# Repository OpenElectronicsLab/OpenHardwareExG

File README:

The OpenHardwareExG is a platform for ECG, EEG, EMG, ENG, EOG, and evoked potential applications.

http://openelectronicslab.github.io/OpenHardwareExG/

The OpenHardwareExG platform was originally developed as part of the eeg-mouse project.
https://github.com/OpenElectronicsLab/eeg-mouse

Software License

GPL v3 or any later version

(The authors may be persuaded to license parts of their contributions
under another FOSS license if GPLv3 is a problem for integration with an
existing established project, for instance linux kernel is GPLv2. Please
contact us.) Hardware and Hardware Documentation License

CERN Open Hardware Licence

(This applies mostly to the kicad-files and scad-files directories)
"Documentation" means schematic diagrams, designs, circuit or circuit
board layouts, mechanical drawings, flow charts and descriptive text,
and other explanatory material that is explicitly stated as being made
available under the conditions of this Licence. The Documentation may be
in any medium, including but not limited to computer files and
representations on paper, film, or any other media.

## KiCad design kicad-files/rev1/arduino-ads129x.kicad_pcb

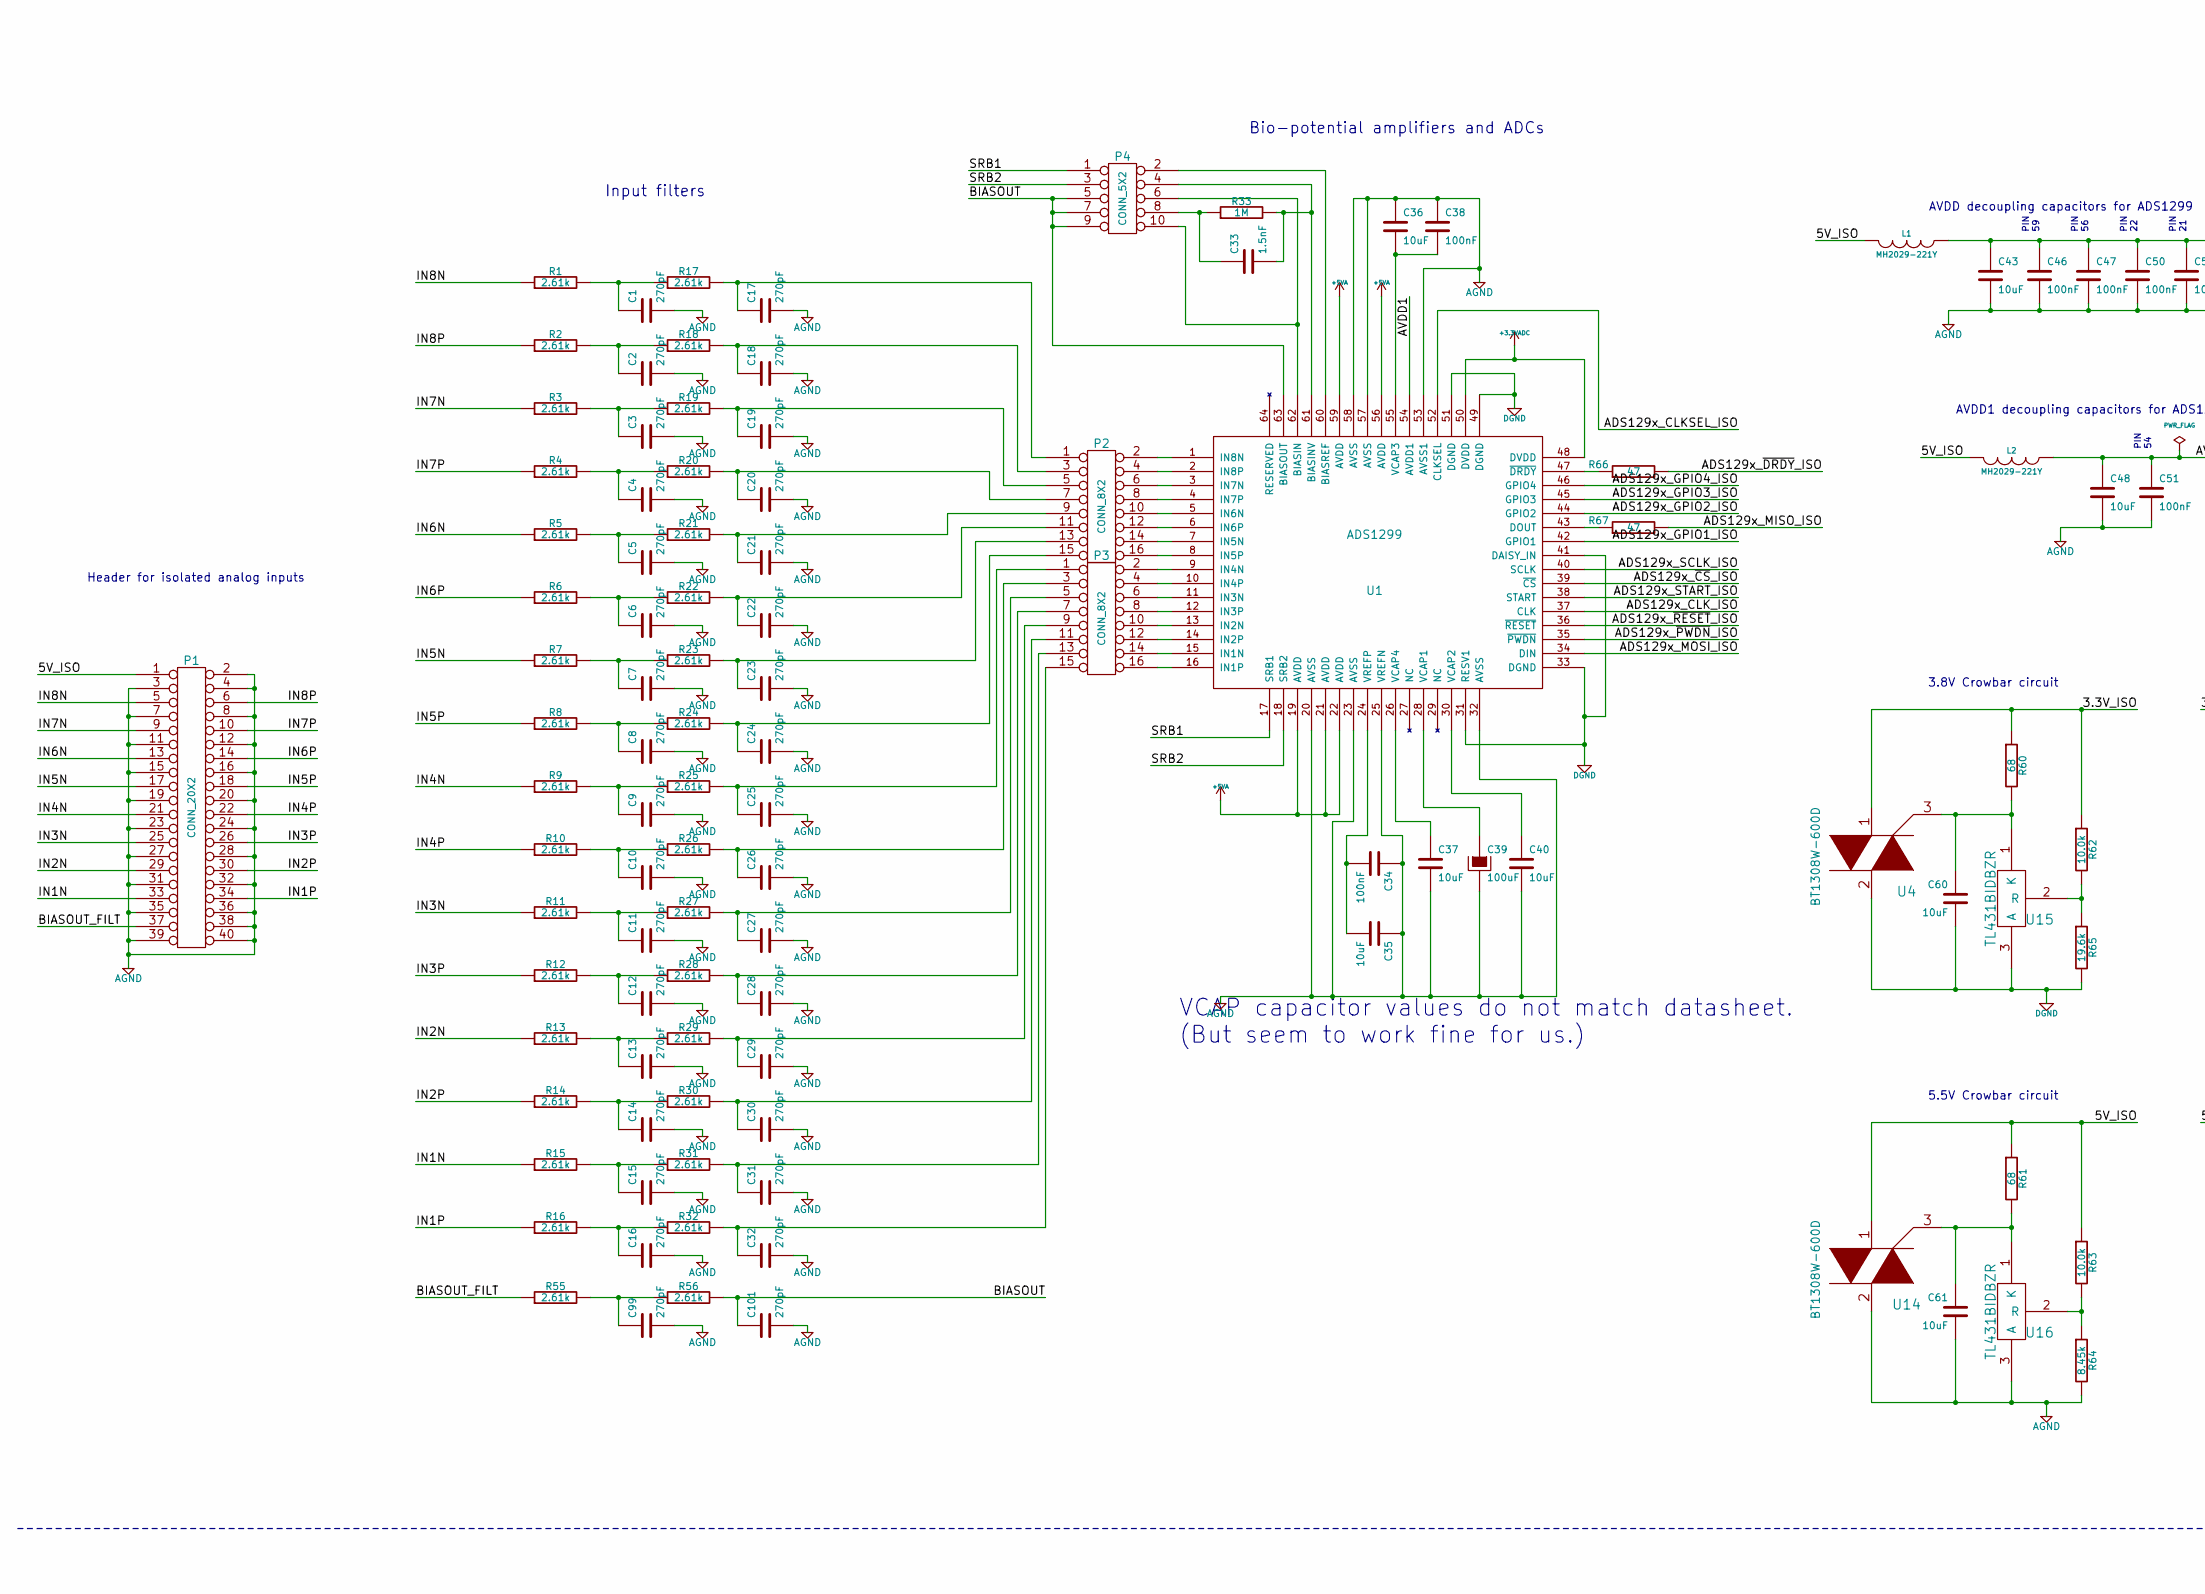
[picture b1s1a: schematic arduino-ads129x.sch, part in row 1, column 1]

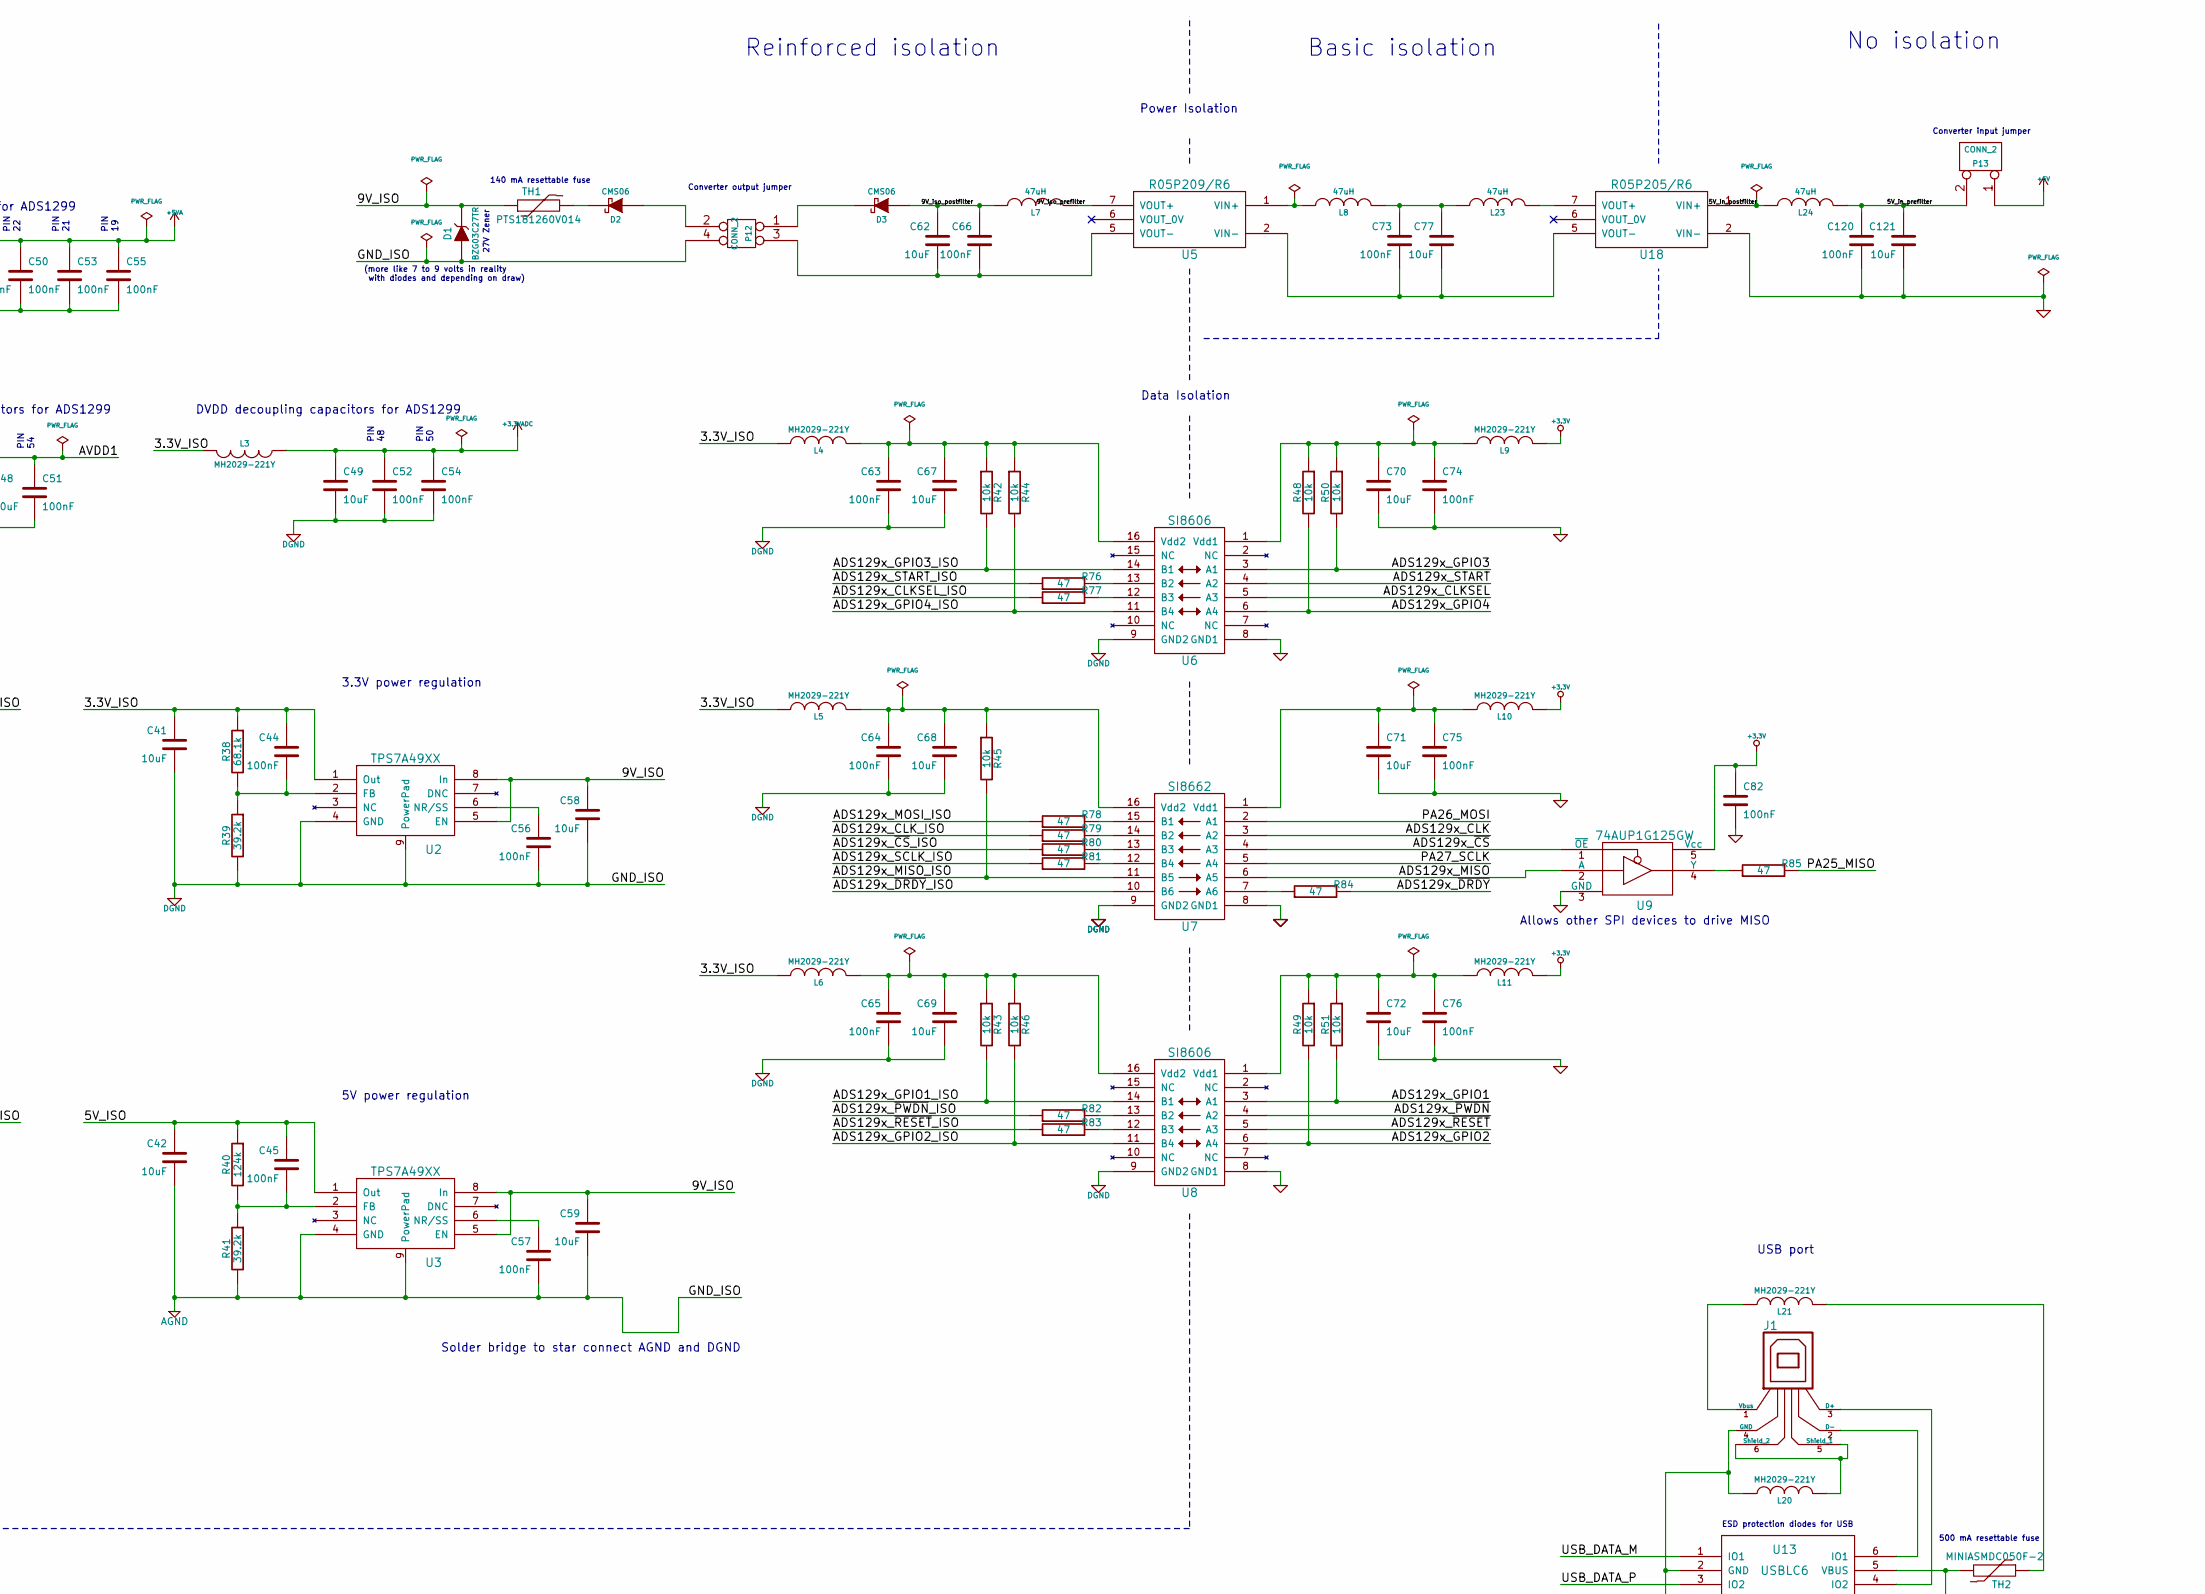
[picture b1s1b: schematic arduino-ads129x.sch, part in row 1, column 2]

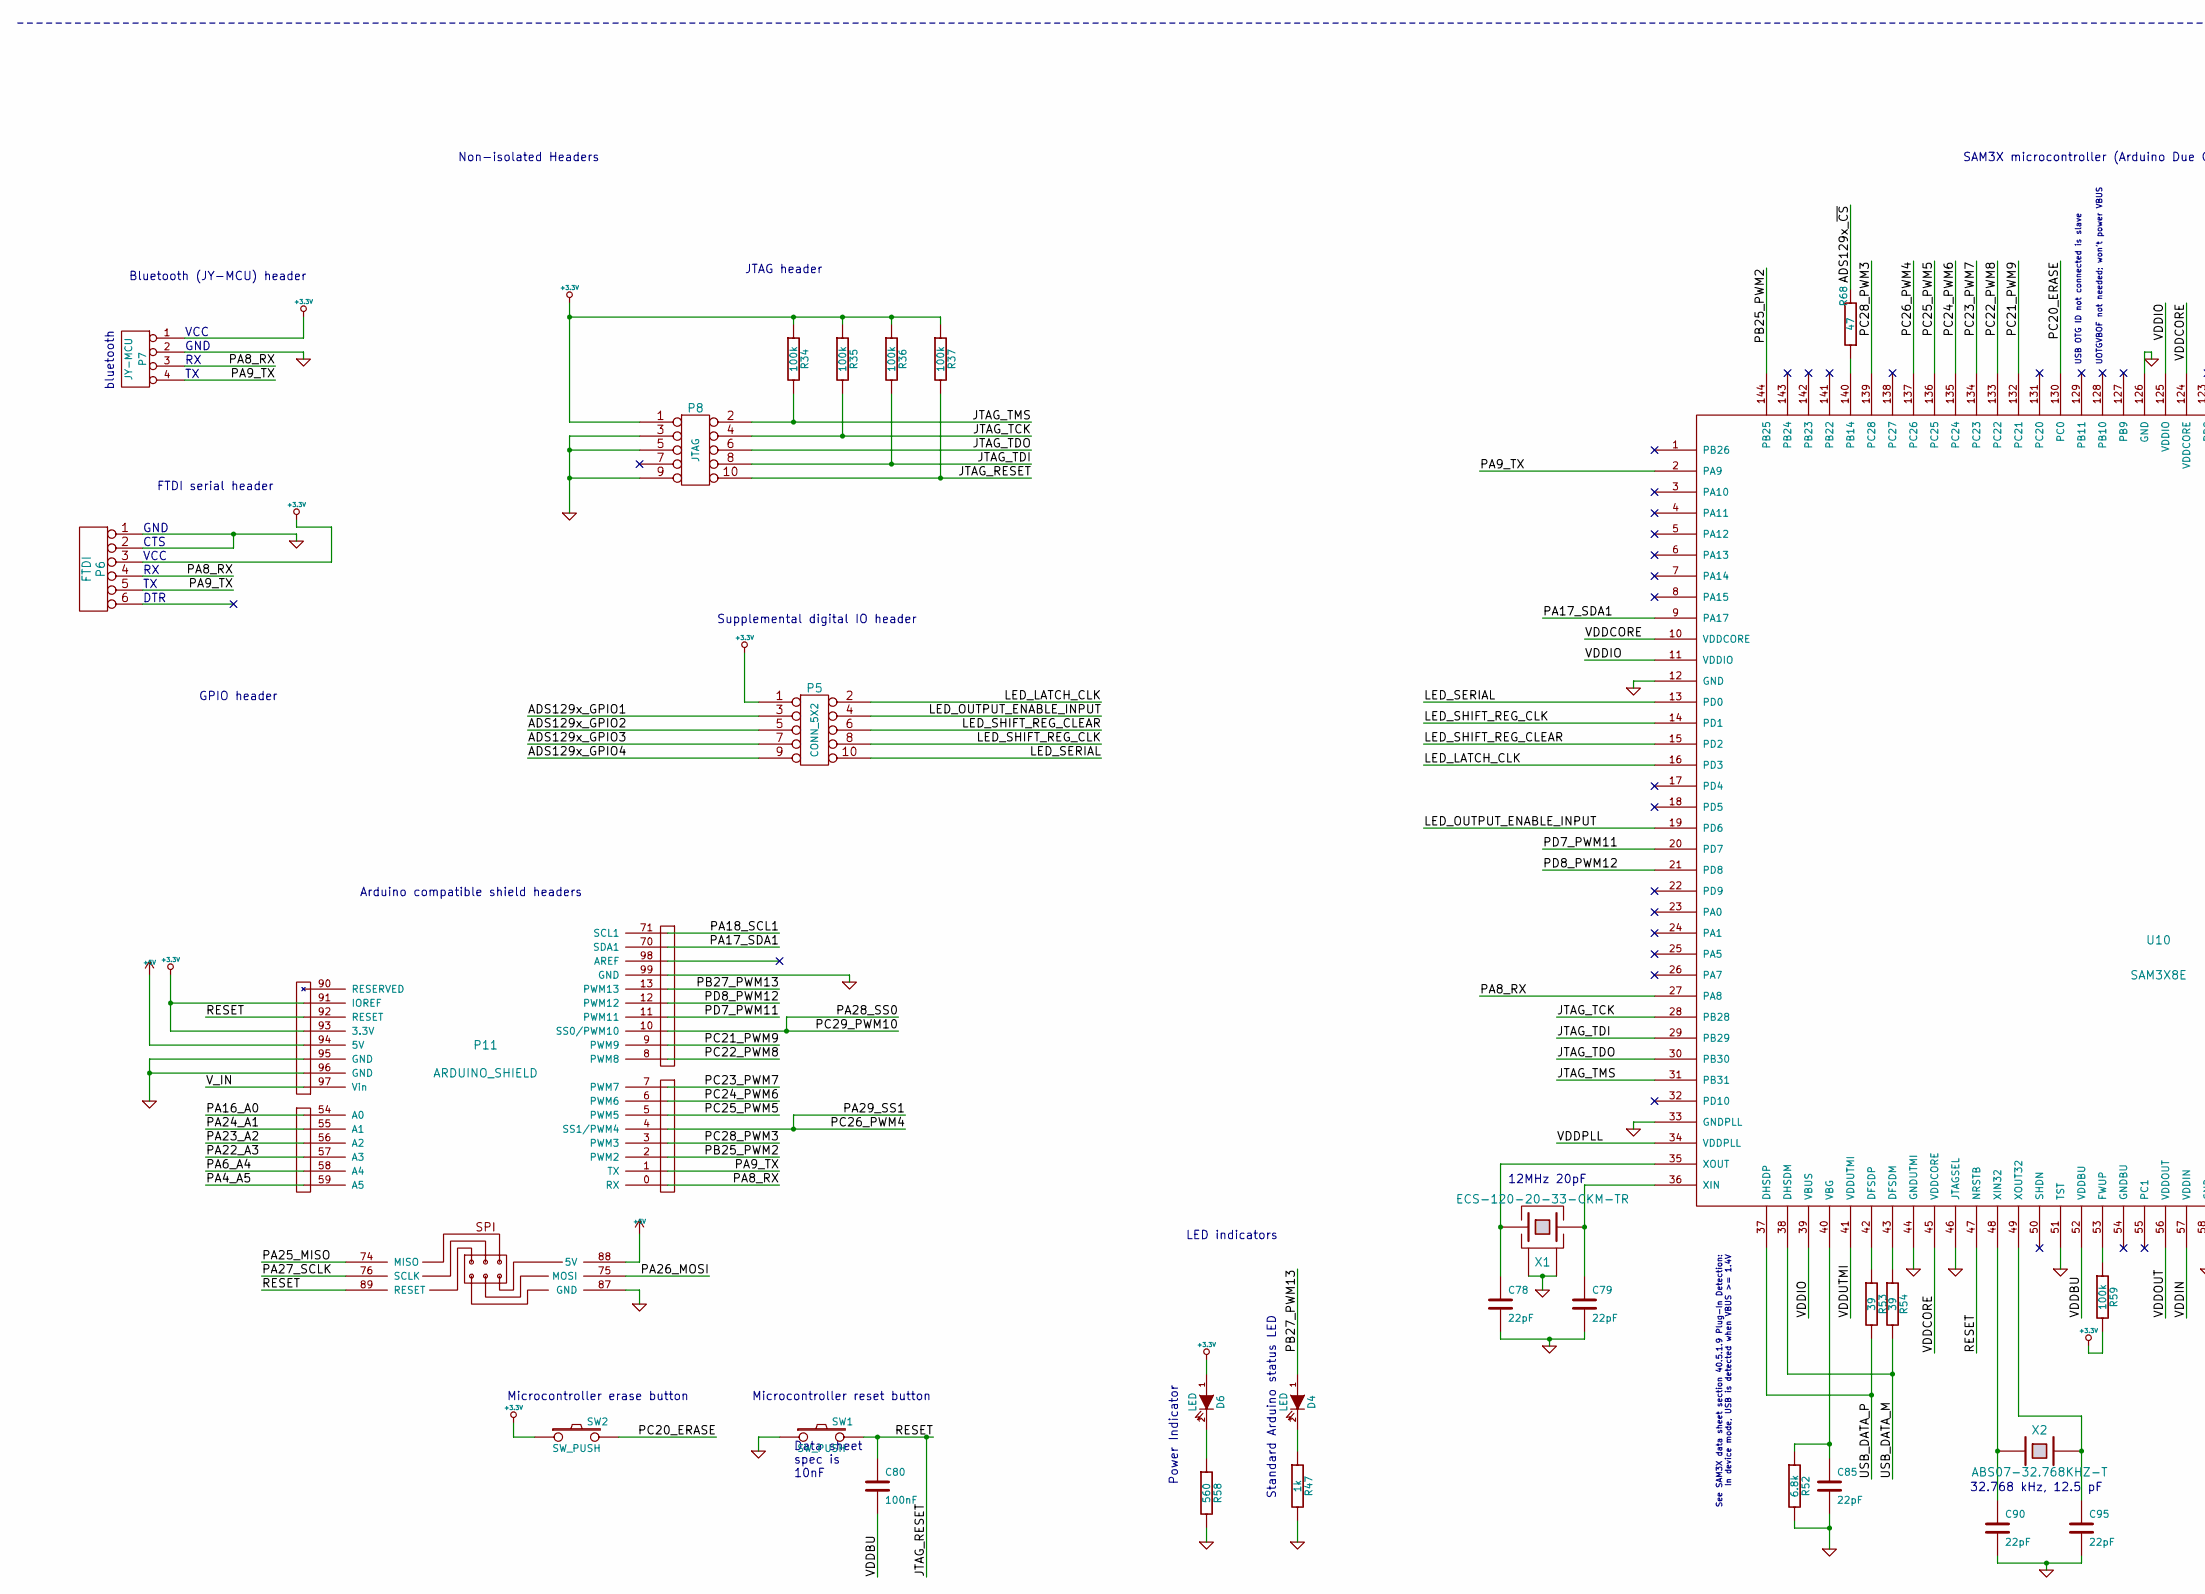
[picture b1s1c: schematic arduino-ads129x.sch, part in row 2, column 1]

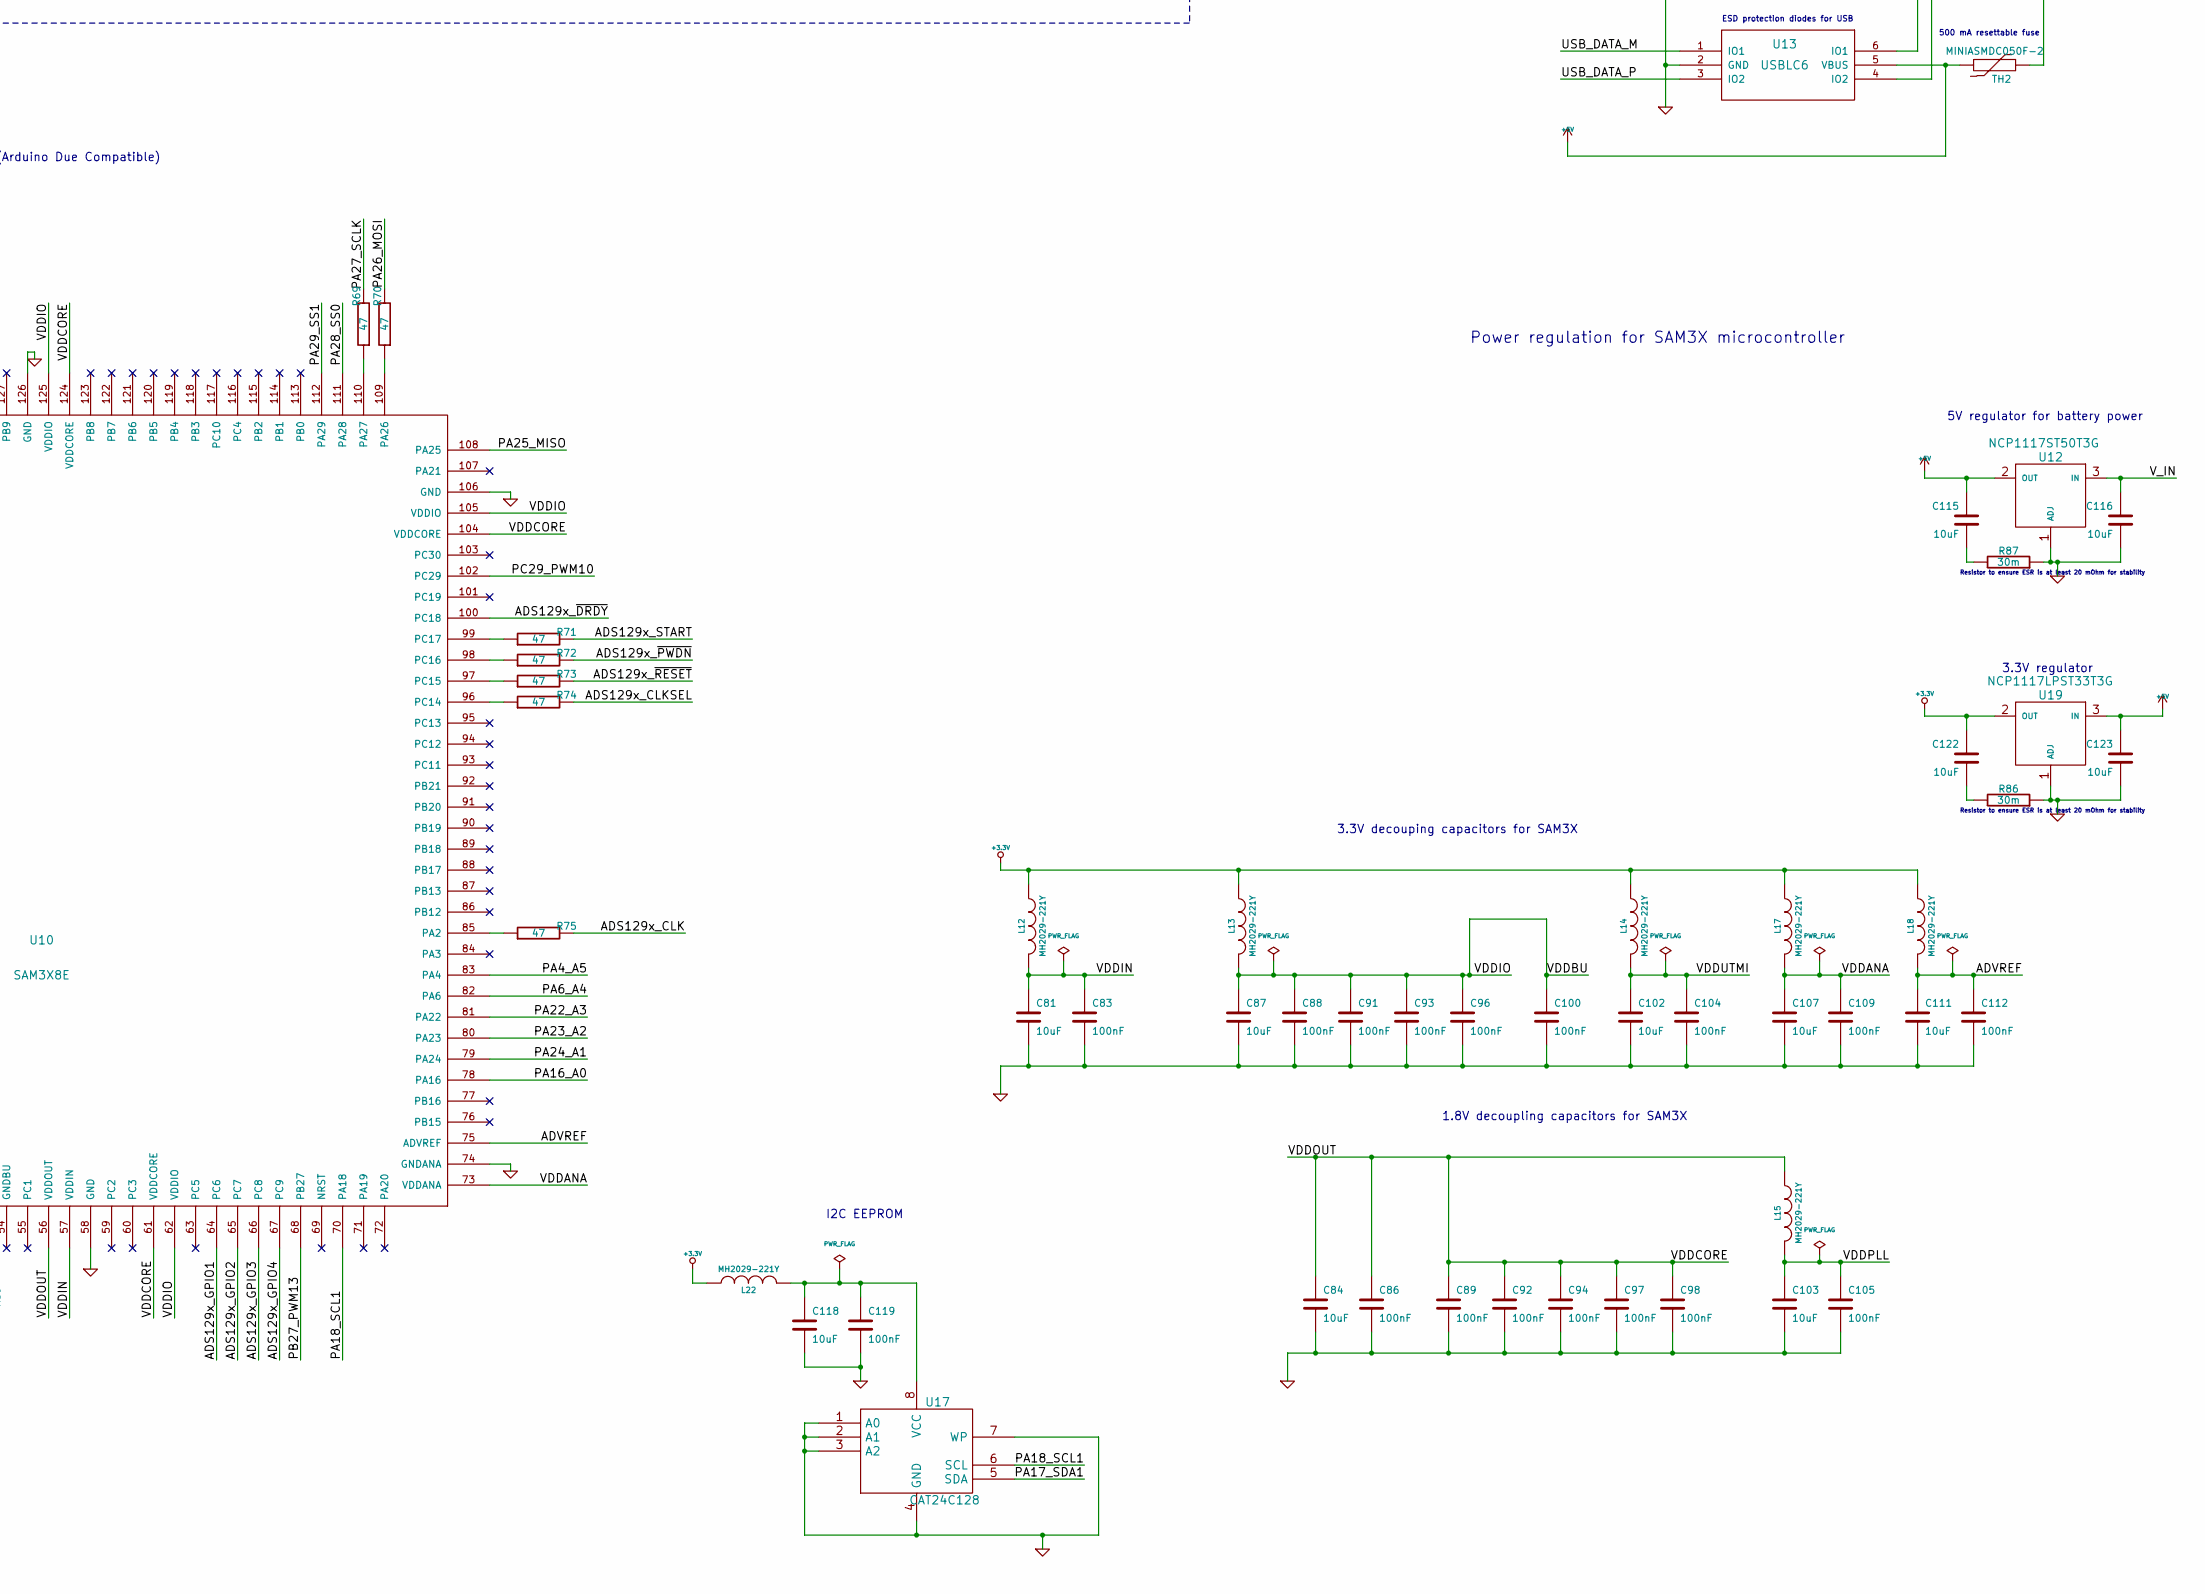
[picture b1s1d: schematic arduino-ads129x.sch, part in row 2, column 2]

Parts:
C1, C2, C3, C4, C5, C6, C7, C8, C9, C10, C11, C12, C13, C14, C15, C16, C17, C18, C19, C20, C21, C22, C23, C24, C25, C26, C27, C28, C29, C30, C31, C32, C99, C101: 270pF; SM0603
C33: 1.5nF; SM0603
C34, C38, C44, C45, C46, C47, C50, C51, C52, C53, C54, C55, C56, C57, C63, C64, C65, C66, C73, C74, C75, C76, C80, C82, C83, C86, C88, C89, C91, C92, C93, C94, C96, C97, C98, C100, C104, C105, C109, C112, C119, C120: 100nF; SM0603
C35, C36, C37, C40, C41, C42, C43, C48, C49, C60, C61, C67, C68, C69, C70, C71, C72, C77, C81, C84, C87, C102, C103, C107, C111, C115, C118, C121, C122, C123: 10uF; SM0805
C39: 100uF; SM2512
C58, C59, C62, C116: 10uF; SM1210
C78, C79, C85, C90, C95: 22pF; SM0603
D1: BZG03C27TR; DO214
D2, D3: CMS06; SM2010
D4, D6: LED; LED-0603
J1: USB; USB_B
L1, L2, L3, L4, L5, L6, L9, L10, L11, L12, L13, L14, L15, L17, L18, L20, L21, L22: MH2029-221Y; SM0805
L7, L8, L23, L24: 47uH; SRR4028
P1: CONN_20X2; PIN_ARRAY_20X2
P2, P3: CONN_8X2; pin_array_8x2
P4, P5: CONN_5X2; PIN_ARRAY_5x2
P6: FTDI; PIN_ARRAY-6X1
P7: JY-MCU; PIN_ARRAY_4x1
P8: JTAG; SMT_PIN_2x5
P11: ARDUINO_SHIELD; arduino_shield
P12: CONN_2; PIN_ARRAY_2X2
P13: CONN_2; PIN_ARRAY_2X1
R1, R2, R3, R4, R5, R6, R7, R8, R9, R10, R11, R12, R13, R14, R15, R16, R17, R18, R19, R20, R21, R22, R23, R24, R25, R26, R27, R28, R29, R30, R31, R32, R55, R56: 2.61k; SM0603
R33: 1M; SM0805
R34, R35, R36, R37, R59: 100k; SM0603
R38: 68.1k; SM0603
R39, R41: 39.2k; SM0603
R40: 124k; SM0603
R42, R43, R44, R45, R46, R48, R49, R50, R51: 10k; SM0603
R47: 1k; SM0603
R52: 6.8k; SM0603
R53, R54: 39; SM0603
R58: 560; SM0603
R60, R61: 68; SM0603
R62, R63: 10.0k; SM0603
R64: 8.45k; SM0603
R65: 19.6k; SM0603
R66, R67, R68, R69, R70, R71, R72, R73, R74, R75, R76, R77, R78, R79, R80, R81, R82, R83, R84, R85: 47; SM0603
R86, R87: 30m; SM0603
SW1, SW2: SW_PUSH; smt-tactile-button
TH1: PTS181260V014; SM1812
TH2: MINIASMDC050F-2; SM1812
U1: ADS1299; TQFP_64
U2, U3: TPS7A49XX; MSOP8_PowerPad
U4, U14: BT1308W-600D; SOT223
U5: R05P209/R6; SIP7_ISOLATOR
U6, U8: SI8606; SO16W
U7: SI8662; SO16W
U9: 74AUP1G125GW; SOT353
U10: SAM3X8E; TQFP144
U12: NCP1117ST50T3G; SOT223
U13: USBLC6; SOT23_6
U15, U16: TL431BIDBZR; SOT23
U17: CAT24C128; SOIC8
U18: R05P205/R6; SIP7_ISOLATOR
U19: NCP1117LPST33T3G; SOT223
X1: ECS-120-20-33-CKM-TR; smt-crystal-3.2x2.5
X2: ABS07-32.768KHZ-T; ABS07

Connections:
+3.3V: C82.1, C122.1, D6.1 (A), L9.2, L10.2, L11.2, L12.1, L13.1, L14.1, L17.1, L18.1, L22.1, P5.1, P6.3, P7.1, P8.1, P11.91 (IOREF), P11.93 (3.3V), R34.1, R35.1, R36.1, R37.1, R59.2, SW2.1, U9.5 (Vcc), U19.2 (OUT)
+3.3VADC: C49.1, C52.1, C54.1, L3.1, U1.48 (DVDD), U1.50 (DVDD)
+5V: C115.1, C123.1, P11.88 (5V), P11.94 (5V), P13.1, TH2.2, U12.2 (OUT), U13.5 (VBUS), U19.3 (IN)
+5VA: C43.1, C46.1, C47.1, C50.1, C53.1, C55.1, L1.1, U1.19 (AVDD), U1.21 (AVDD), U1.22 (AVDD), U1.56 (AVDD), U1.59 (AVDD)
/3.3V_ISO: C41.1, C44.1, L3.2, L4.2, L5.2, L6.2, R38.1, R60.1, R62.1, U2.1 (Out), U4.1
/5V_ISO: C42.1, C45.1, L1.2, L2.2, P1.1, R40.1, R61.1, R63.1, U3.1 (Out), U14.1
/5V_in_prefilter: C120.1, C121.1, L24.1, P13.2 (PM)
/9V_ISO: C58.1, C59.1, D1.2 (K), TH1.1, U2.5 (EN), U2.8 (In), U3.5 (EN), U3.8 (In)
/9V_iso_postfilter: C62.1, C66.1, D3.1 (A), L7.2
/ADS129x_CLK: R75.2, U7.3 (A2)
/ADS129x_CLKSEL: R74.2, U6.5 (A3)
/ADS129x_CLKSEL_ISO: R77.1, U1.52 (CLKSEL)
/ADS129x_CLK_ISO: R79.1, U1.37 (CLK)
/ADS129x_GPIO1: P5.3, R51.2, U8.3 (A1), U10.64 (PC6)
/ADS129x_GPIO1_ISO: R43.2, U1.42 (GPIO1), U8.14 (B1)
/ADS129x_GPIO2: P5.5, R49.2, U8.6 (A4), U10.65 (PC7)
/ADS129x_GPIO2_ISO: R46.2, U1.44 (GPIO2), U8.11 (B4)
/ADS129x_GPIO3: P5.7, R50.2, U6.3 (A1), U10.66 (PC8)
/ADS129x_GPIO3_ISO: R42.2, U1.45 (GPIO3), U6.14 (B1)
/ADS129x_GPIO4: P5.9, R48.2, U6.6 (A4), U10.67 (PC9)
/ADS129x_GPIO4_ISO: R44.2, U1.46 (GPIO4), U6.11 (B4)
/ADS129x_MISO: U7.6 (A5), U9.2 (A)
/ADS129x_MISO_ISO: R45.2, R67.2, U7.11 (B5)
/ADS129x_MOSI_ISO: R78.1, U1.34 (DIN)
/ADS129x_SCLK_ISO: R81.1, U1.40 (SCLK)
/ADS129x_START: R71.2, U6.4 (A2)
/ADS129x_START_ISO: R76.1, U1.38 (START)
/ADS129x_~CS~: R68.2, U7.4 (A3), U9.1 (~OE~)
/ADS129x_~CS~_ISO: R80.1, U1.39 (~CS~)
/ADS129x_~DRDY~: R84.2, U10.100 (PC18)
/ADS129x_~DRDY~_ISO: R66.2, U7.10 (B6)
/ADS129x_~PWDN~: R72.2, U8.4 (A2)
/ADS129x_~PWDN~_ISO: R82.1, U1.35 (~PWDN~)
/ADS129x_~RESET~: R73.2, U8.5 (A3)
/ADS129x_~RESET~_ISO: R83.1, U1.36 (~RESET~)
/ADVREF: C111.1, C112.1, L18.2, U10.75 (ADVREF)
/AVDD1: C48.1, C51.1, L2.1, U1.54 (AVDD1)
/BIASOUT: C101.1, P4.5, P4.7, P4.9, R56.2, U1.63 (BIASOUT)
/BIASOUT_FILT: P1.37, R55.1
/IN1N: P1.33, R15.1
/IN1P: P1.34, R16.1
/IN2N: P1.29, R13.1
/IN2P: P1.30, R14.1
/IN3N: P1.25, R11.1
/IN3P: P1.26, R12.1
/IN4N: P1.21, R9.1
/IN4P: P1.22, R10.1
/IN5N: P1.17, R7.1
/IN5P: P1.18, R8.1
/IN6N: P1.13, R5.1
/IN6P: P1.14, R6.1
/IN7N: P1.9, R3.1
/IN7P: P1.10, R4.1
/IN8N: P1.5, R1.1
/IN8P: P1.6, R2.1
/JTAG_RESET: C80.1, P8.10, P11.89 (RESET), P11.92 (RESET), R37.2, SW1.2, U10.47 (NRSTB)
/JTAG_TCK: P8.4, R35.2, U10.28 (PB28)
/JTAG_TDI: P8.8, R36.2, U10.29 (PB29)
/JTAG_TDO: P8.6, U10.30 (PB30)
/JTAG_TMS: P8.2, R34.2, U10.31 (PB31)
/LED_LATCH_CLK: P5.2, U10.16 (PD3)
/LED_OUTPUT_ENABLE_INPUT: P5.4, U10.19 (PD6)
/LED_SERIAL: P5.10, U10.13 (PD0)
/LED_SHIFT_REG_CLEAR: P5.6, U10.15 (PD2)
/LED_SHIFT_REG_CLK: P5.8, U10.14 (PD1)
/PA4_A5: P11.59 (A5), U10.83 (PA4)
/PA6_A4: P11.58 (A4), U10.82 (PA6)
/PA8_RX: P6.4, P7.3, P11.0 (RX), U10.27 (PA8)
/PA9_TX: P6.5, P7.4, P11.1 (TX), U10.2 (PA9)
/PA16_A0: P11.54 (A0), U10.78 (PA16)
/PA17_SDA1: P11.70 (SDA1), U10.9 (PA17), U17.5 (SDA)
/PA18_SCL1: P11.71 (SCL1), U10.70 (PA18), U17.6 (SCL)
/PA22_A3: P11.57 (A3), U10.81 (PA22)
/PA23_A2: P11.56 (A2), U10.80 (PA23)
/PA24_A1: P11.55 (A1), U10.79 (PA24)
/PA25_MISO: P11.74 (MISO), R85.2, U10.108 (PA25)
/PA26_MOSI: P11.75 (MOSI), R70.2, U7.2 (A1)
/PA27_SCLK: P11.76 (SCLK), R69.2, U7.5 (A4)
/PA28_SS0: P11.10 (SS0/PWM10), U10.102 (PC29), U10.111 (PA28)
/PA29_SS1: P11.4 (SS1/PWM4), U10.112 (PA29), U10.137 (PC26)
/PB25_PWM2: P11.2 (PWM2), U10.144 (PB25)
/PB27_PWM13: D4.1 (A), P11.13 (PWM13), U10.68 (PB27)
/PC20_ERASE: SW2.2, U10.130 (PC0)
/PC21_PWM9: P11.9 (PWM9), U10.132 (PC21)
/PC22_PWM8: P11.8 (PWM8), U10.133 (PC22)
/PC23_PWM7: P11.7 (PWM7), U10.134 (PC23)
/PC24_PWM6: P11.6 (PWM6), U10.135 (PC24)
/PC25_PWM5: P11.5 (PWM5), U10.136 (PC25)
/PC28_PWM3: P11.3 (PWM3), U10.139 (PC28)
/PD7_PWM11: P11.11 (PWM11), U10.20 (PD7)
/PD8_PWM12: P11.12 (PWM12), U10.21 (PD8)
/SRB1: P4.1, U1.17 (SRB1)
/SRB2: P4.3, U1.18 (SRB2)
/USB_DATA_M: R54.2, U10.38 (DHSDM), U13.1 (IO1)
/USB_DATA_P: R53.2, U10.37 (DHSDP), U13.3 (IO2)
/VDDANA: C107.1, C109.1, L17.2, U10.73 (VDDANA)
/VDDBU: C80.2, C87.1, C88.1, C91.1, C93.1, C96.1, C100.1, L13.2, U10.11 (VDDIO), U10.39 (VBUS), U10.52 (VDDBU), U10.62 (VDDIO), U10.105 (VDDIO), U10.125 (VDDIO)
/VDDCORE: C84.1, C86.1, C89.1, C92.1, C94.1, C97.1, C98.1, L15.1, U10.10 (VDDCORE), U10.45 (VDDCORE), U10.56 (VDDOUT), U10.61 (VDDCORE), U10.104 (VDDCORE), U10.124 (VDDCORE)
/VDDIN: C81.1, C83.1, L12.2, U10.57 (VDDIN)
/VDDPLL: C103.1, C105.1, L15.2, U10.34 (VDDPLL)
/VDDUTMI: C102.1, C104.1, L14.2, U10.41 (VDDUTMI)
/V_IN: C116.1, P11.97 (Vin), U12.3 (IN)
AGND: C1.2, C2.2, C3.2, C4.2, C5.2, C6.2, C7.2, C8.2, C9.2, C10.2, C11.2, C12.2, C13.2, C14.2, C15.2, C16.2, C17.2, C18.2, C19.2, C20.2, C21.2, C22.2, C23.2, C24.2, C25.2, C26.2, C27.2, C28.2, C29.2, C30.2, C31.2, C32.2, C34.1, C35.1, C36.1, C37.2, C38.1, C39.2, C40.2, C41.2, C42.2, C43.2, C46.2, C47.2, C48.2, C49.2, C50.2, C51.2, C52.2, C53.2, C54.2, C55.2, C56.2, C57.2, C58.2, C59.2, C60.2, C61.2, C63.2, C64.2, C65.2, C67.2, C68.2, C69.2, C99.2, C101.2, D1.1 (A), P1.2, P1.3, P1.4, P1.7, P1.8, P1.11, P1.12, P1.15, P1.16, P1.19, P1.20, P1.23, P1.24, P1.27, P1.28, P1.31, P1.32, P1.35, P1.36, P1.38, P1.39, P1.40, P12.4, R39.2, R41.2, R64.2, R65.2, U1.20 (AVSS), U1.23 (AVSS), U1.25 (VREFN), U1.31 (RESV1), U1.32 (AVSS), U1.33 (DGND), U1.41 (DAISY_IN), U1.49 (DGND), U1.51 (DGND), U1.53 (AVSS1), U1.57 (AVSS), U1.58 (AVSS), U2.4 (GND), U2.9 (PowerPad), U3.4 (GND), U3.9 (PowerPad), U4.2, U6.9 (GND2), U7.9 (GND2), U8.9 (GND2), U14.2, U15.3 (A), U16.3 (A)
GND: C70.2, C71.2, C72.2, C74.2, C75.2, C76.2, C78.2, C79.2, C81.2, C82.2, C83.2, C84.2, C85.2, C86.2, C87.2, C88.2, C89.2, C90.2, C91.2, C92.2, C93.2, C94.2, C95.2, C96.2, C97.2, C98.2, C100.2, C102.2, C103.2, C104.2, C105.2, C107.2, C109.2, C111.2, C112.2, C116.2, C118.2, C119.2, C120.2, C121.2, C123.2, J1.4 (GND), L20.1, P6.1, P6.2, P7.2, P8.3, P8.5, P8.9, P11.87 (GND), P11.95 (GND), P11.96 (GND), P11.99 (GND), R47.2, R52.2, R58.2, R86.1, R87.1, SW1.1, U6.8 (GND1), U7.8 (GND1), U8.8 (GND1), U9.3 (GND), U10.12 (GND), U10.33 (GNDPLL), U10.44 (GNDUTMI), U10.46 (JTAGSEL), U10.51 (TST), U10.58 (GND), U10.74 (GNDANA), U10.106 (GND), U10.126 (GND), U12.1 (ADJ), U13.2 (GND), U17.1 (A0), U17.2 (A1), U17.3 (A2), U17.4 (GND), U17.7 (WP), U18.2 (VIN-), U19.1 (ADJ), X1.2 (GND1), X1.4 (GND2)
unnamed: C72.1, C76.1, L11.1, R49.1, R51.1, U8.1 (Vdd1)
unnamed: C65.1, C69.1, L6.1, R43.1, R46.1, U8.16 (Vdd2)
unnamed: C64.1, C68.1, L5.1, R45.1, U7.16 (Vdd2)
unnamed: C45.2, R40.2, R41.1, U3.2 (FB)
unnamed: C56.1, U2.6 (NR/SS)
unnamed: C57.1, U3.6 (NR/SS)
unnamed: C63.1, C67.1, L4.1, R42.1, R44.1, U6.16 (Vdd2)
unnamed: C118.1, C119.1, L22.2, U17.8 (VCC)
unnamed: L24.2, U18.1 (VIN+)
unnamed: P4.6, P4.10, U1.62 (BIASIN)
unnamed: R62.2, R65.1, U15.2 (R)
unnamed: C60.1, R60.2, U4.3, U15.1 (K)
unnamed: C79.1, U10.36 (XIN), X1.3
unnamed: D3.2 (K), P12.1
unnamed: P4.2, U1.60 (BIASREF)
unnamed: J1.3 (D+), U13.4 (IO2)
unnamed: D4.2 (K), R47.1
unnamed: C14.1, R14.2, R30.1
unnamed: C25.1, P3.1, R25.2
unnamed: C9.1, R9.2, R25.1
unnamed: C24.1, P2.15, R24.2
unnamed: C8.1, R8.2, R24.1
unnamed: C31.1, P3.13, R31.2
unnamed: C15.1, R15.2, R31.1
unnamed: C39.1, U1.28 (VCAP1)
unnamed: C33.1, P4.8, R33.1
unnamed: C28.1, P3.7, R28.2
unnamed: C40.1, U1.30 (VCAP2)
unnamed: P2.10, U1.5 (IN6N)
unnamed: C20.1, P2.7, R20.2
unnamed: P2.12, U1.6 (IN6P)
unnamed: P2.14, U1.7 (IN5N)
unnamed: P2.16, U1.8 (IN5P)
unnamed: P2.2, U1.1 (IN8N)
unnamed: P2.4, U1.2 (IN8P)
unnamed: P2.6, U1.3 (IN7N)
unnamed: P2.8, U1.4 (IN7P)
unnamed: R66.1, U1.47 (~DRDY~)
unnamed: J1.1 (Vbus), L21.1
unnamed: J1.2 (D-), U13.6 (IO1)
unnamed: R67.1, U1.43 (DOUT)
unnamed: C34.2, C35.2, U1.24 (VREFP)
unnamed: C36.2, C38.2, U1.55 (VCAP3)
unnamed: P3.16, U1.16 (IN1P)
unnamed: C37.1, U1.26 (VCAP4)
unnamed: C18.1, P2.3, R18.2
unnamed: C2.1, R2.2, R18.1
unnamed: C21.1, P2.9, R21.2
unnamed: C5.1, R5.2, R21.1
unnamed: C17.1, P2.1, R17.2
unnamed: P3.4, U1.10 (IN4P)
unnamed: P3.2, U1.9 (IN4N)
unnamed: C26.1, P3.3, R26.2
unnamed: P3.6, U1.11 (IN3N)
unnamed: P3.8, U1.12 (IN3P)
unnamed: P3.10, U1.13 (IN2N)
unnamed: C30.1, P3.11, R30.2
unnamed: P3.12, U1.14 (IN2P)
unnamed: P3.14, U1.15 (IN1N)
unnamed: C19.1, P2.5, R19.2
unnamed: C3.1, R3.2, R19.1
unnamed: C73.1, C77.1, L8.1, L23.2
unnamed: L7.1, U5.7 (VOUT+)
unnamed: C73.2, C77.2, U5.2 (VIN-), U18.5 (VOUT-)
unnamed: J1.5 (Shield_1), J1.6 (Shield_2), L20.2
unnamed: D2.1 (A), P12.2
unnamed: L21.2, TH2.1
unnamed: C90.1, U10.48 (XIN32), X2.1
unnamed: D6.2 (K), R58.1
unnamed: D2.2 (K), TH1.2
unnamed: C85.1, R52.1, U10.40 (VBG)
unnamed: C95.1, U10.49 (XOUT32), X2.2
unnamed: R72.1, U10.98 (PC16)
unnamed: R71.1, U10.99 (PC17)
unnamed: R69.1, U10.110 (PA27)
unnamed: R68.1, U10.140 (PB14)
unnamed: R75.1, U10.85 (PA2)
unnamed: R74.1, U10.96 (PC14)
unnamed: R73.1, U10.97 (PC15)
unnamed: R54.1, U10.43 (DFSDM)
unnamed: R59.1, U10.53 (FWUP)
unnamed: C78.1, U10.35 (XOUT), X1.1
unnamed: R76.2, U6.13 (B2)
unnamed: R53.1, U10.42 (DFSDP)
unnamed: C4.1, R4.2, R20.1
unnamed: C10.1, R10.2, R26.1
unnamed: C27.1, P3.5, R27.2
unnamed: C11.1, R11.2, R27.1
unnamed: C29.1, P3.9, R29.2
unnamed: C13.1, R13.2, R29.1
unnamed: C12.1, R12.2, R28.1
unnamed: C1.1, R1.2, R17.1
unnamed: C22.1, P2.11, R22.2
unnamed: C6.1, R6.2, R22.1
unnamed: C16.1, R16.2, R32.1
unnamed: C32.1, P3.15, R32.2
unnamed: C23.1, P2.13, R23.2
unnamed: C7.1, R7.2, R23.1
unnamed: C99.1, R55.2, R56.1
unnamed: C115.2, R87.2
unnamed: C61.1, R61.2, U14.3, U16.1 (K)
unnamed: R63.2, R64.1, U16.2 (R)
unnamed: C33.2, P4.4, R33.2, U1.61 (BIASINV)
unnamed: C44.2, R38.2, R39.1, U2.2 (FB)
unnamed: R85.1, U9.4 (Y)
unnamed: R84.1, U7.7 (A6)
unnamed: R81.2, U7.12 (B4)
unnamed: R80.2, U7.13 (B3)
unnamed: R78.2, U7.15 (B1)
unnamed: R79.2, U7.14 (B2)
unnamed: R82.2, U8.13 (B2)
unnamed: R83.2, U8.12 (B3)
unnamed: R77.2, U6.12 (B3)
unnamed: C122.2, R86.2
unnamed: L23.1, U18.7 (VOUT+)
unnamed: R70.1, U10.109 (PA26)
unnamed: L8.2, U5.1 (VIN+)
unnamed: C62.2, C66.2, P12.3, U5.5 (VOUT-)
unnamed: C70.1, C74.1, L9.1, R48.1, R50.1, U6.1 (Vdd1)
unnamed: C71.1, C75.1, L10.1, U7.1 (Vdd1)

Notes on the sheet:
Microcontroller erase button
Solder bridge to star connect AGND and DGND
Resistor to ensure ESR is at least 20 mOhm for stability
3.3V regulator
Basic isolation
I2C EEPROM
12MHz 20pF
32.768 kHz, 12.5 pF
Microcontroller reset button
Power regulation for SAM3X microcontroller
SAM3X microcontroller (Arduino Due Compatible)
Standard Arduino status LED
Power Indicator
LED indicators
Non-isolated Headers
Arduino compatible shield headers
Supplemental digital IO header
Bluetooth (JY-MCU) header
FTDI serial header
GPIO header
JTAG header
1.8V decoupling capacitors for SAM3X
3.3V decouping capacitors for SAM3X
USB port
Header for isolated analog inputs
Input filters
Bio-potential amplifiers and ADCs
ESD protection diodes for USB
500 mA resettable fuse
140 mA resettable fuse
27V Zener
bluetooth
3.8V Crowbar circuit
5.5V Crowbar circuit
No isolation
Reinforced isolation
Allows other SPI devices to drive MISO
5V regulator for battery power
PIN 48
PIN 50

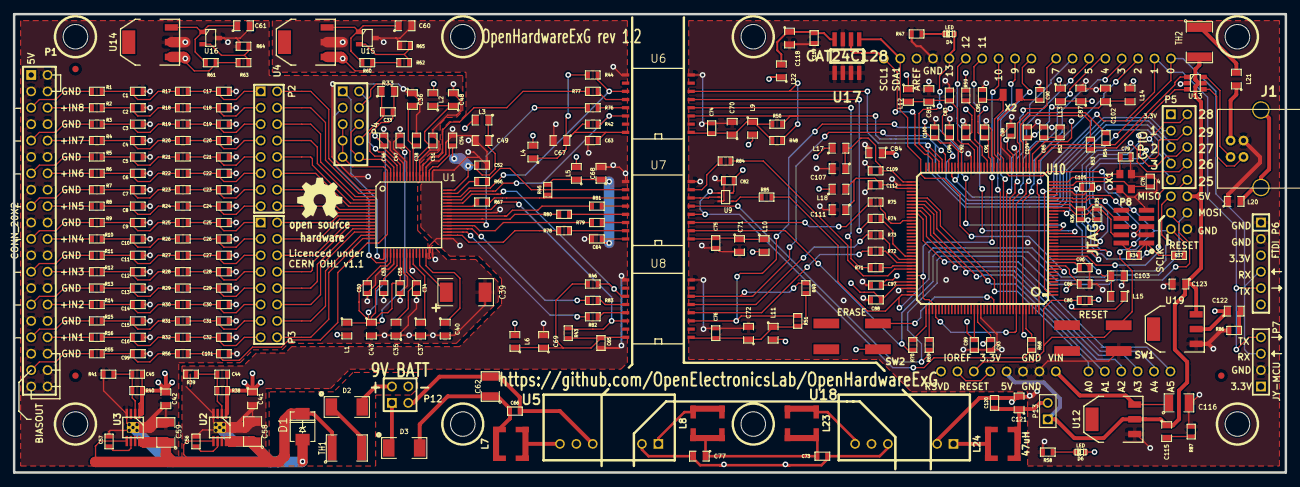
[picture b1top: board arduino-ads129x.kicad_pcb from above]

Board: 4 copper layers, 197.0 x 71.0 mm, 277 parts (0 on the bottom side), 224 nets.

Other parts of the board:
Hole_M3, Hole_M3#2, Hole_M3#3, Hole_M3#4, Hole_M3#5, Hole_M3#6, Hole_M3#7, Hole_M3#8: VAL**; Hole_M3
fiducial_mark: VAL**; fiducial_mark
fiducial_mark#2, fiducial_mark#3: VAL**; fiducial_mark

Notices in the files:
kicad-files/rev1/arduino-ads129x.kicad_pcb:
Licenced under
CERN OHL v1.1
kicad-files/rev1/patch-shield-analog.kicad_pcb:
Licensed under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
